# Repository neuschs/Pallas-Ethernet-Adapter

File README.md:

# Pallas-Ethernet-Adapter
Open source PCIe ethernet adapter based on LAN7430

More information can be found on my blog: https://sebis-workshop.de/uncategorized/pallas-ethernet-adapter/

# Ordering and production parameters
So far I've just ordered the PCBAs and waiting to test my prototypes.
In the folder jlcpcb are the files from this KiCAD plugin located:
https://github.com/Bouni/kicad-jlcpcb-tools

Including position correction for some parts so the pick'n'place file is correct (please check before usage).

# Credits
Thanks to the KiCAD PCIe template project:
https://github.com/lucanastasio/PCIexpress-KiCad

# License
All datasheets are just for documentational pruposes here. All credits go to the companys which distributed them initially.

The Logo - the Pallas Cat - may not be redistributed, made public elsewhere or modified and is property of the author. 

This describes Open Hardware and is licensed under the CERN OHL v.1.2.
You may redistribute and modify this under the terms of the CERN OHL v.1.2. (http://ohwr.org/cernohl). This is distributed WITHOUT ANY EXPRESS OR IMPLIED WARRANTY, INCLUDING OF MERCHANTABILITY, SATISFACTORY QUALITY AND FITNESS FOR A PARTICULAR PURPOSE. Please see the CERN OHL v.1.2 for applicable conditions.

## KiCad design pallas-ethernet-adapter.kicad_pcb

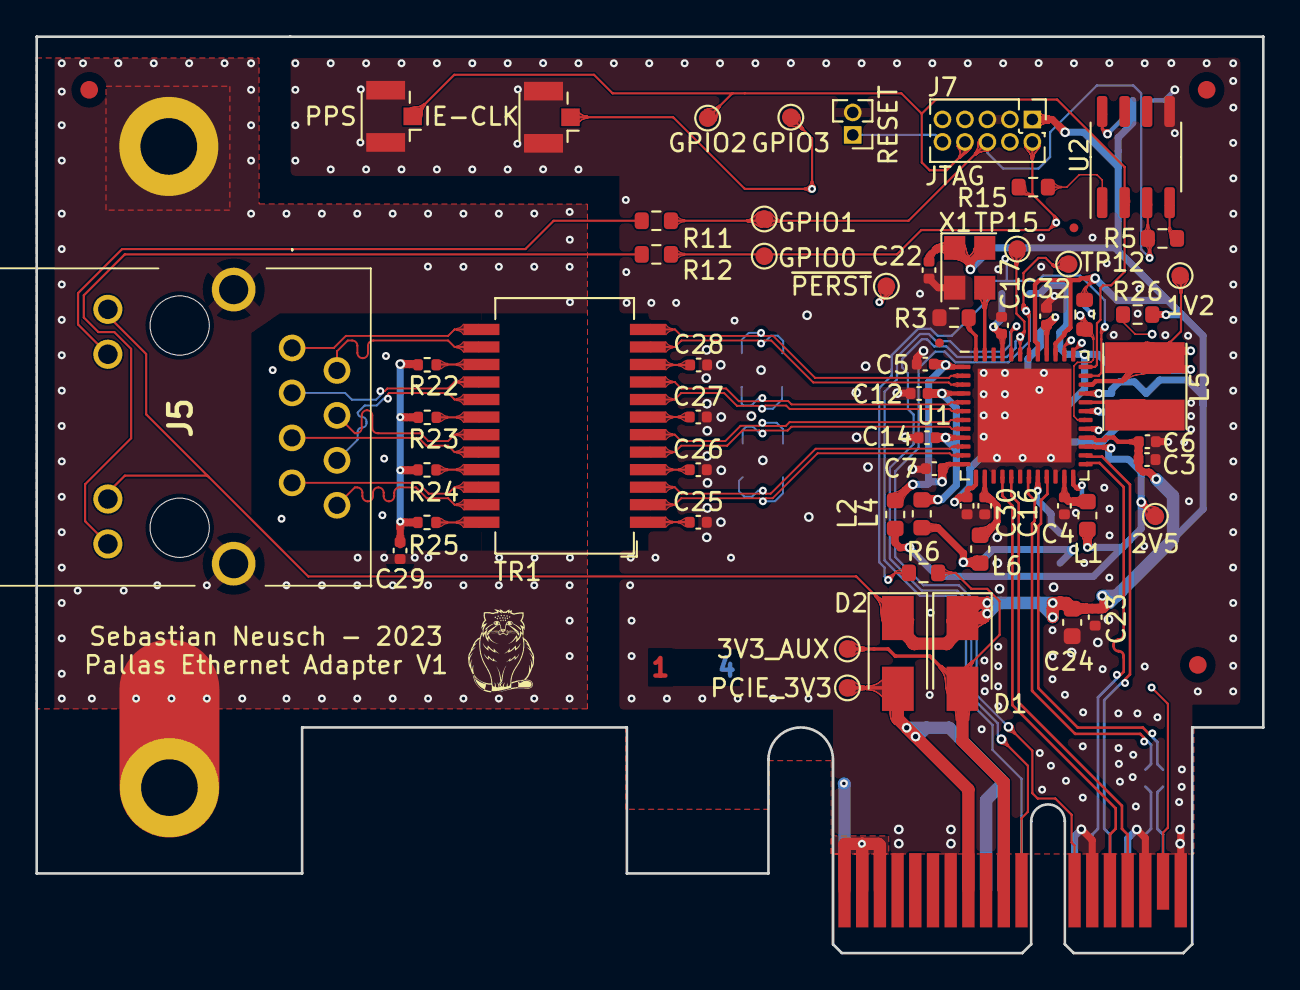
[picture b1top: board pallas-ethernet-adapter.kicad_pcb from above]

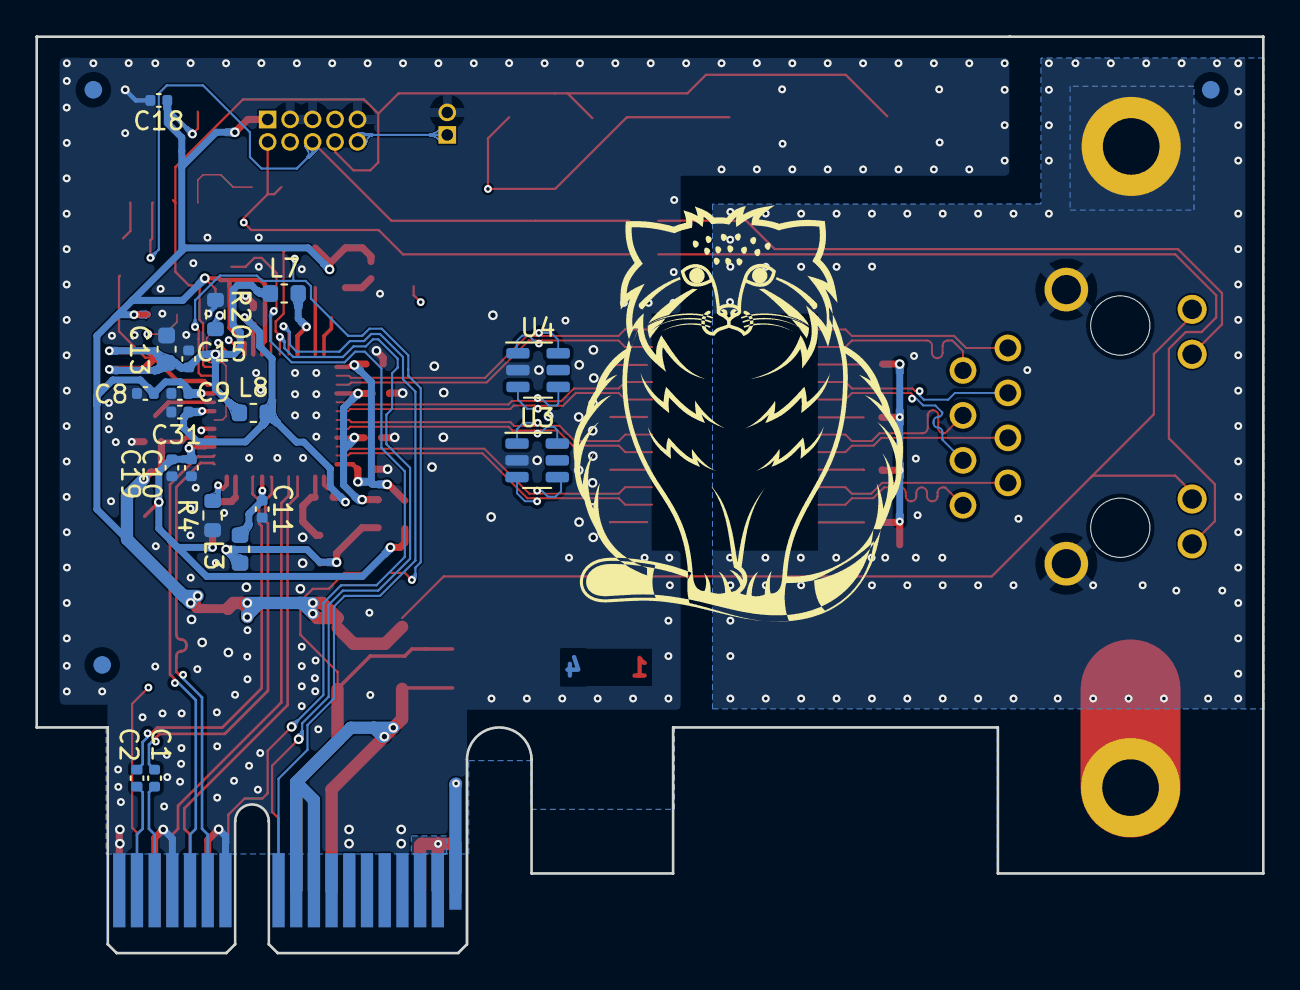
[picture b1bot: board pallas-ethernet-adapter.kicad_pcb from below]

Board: 4 copper layers, 69.3 x 51.8 mm, 88 parts (21 on the bottom side), 66 nets.

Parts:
C1, C2: 100n; C_0402_1005Metric
C3, C8: 4.7uF; C_0402_1005Metric
C4, C5, C6, C7, C9, C11, C12, C14, C15, C16, C17, C18, C19, C22, C23, C25, C26, C27, C28, C29, C30, C31, C32: 100nF; C_0402_1005Metric
C10: 1uF; C_0402_1005Metric
C13, C24: 10uF; C_0603_1608Metric
D1, D2: SS14; D_SMA
FID1, FID2, FID3, FID4, FID5, FID6: Fiducial; Fiducial_1mm_Mask2mm
FID7, FID8: Fiducial; Fiducial_0.5mm_Mask1mm
H1, H2: PCIE_Bracket_Hole; MountingHole_3.2mm_M3_DIN965_Pad
J1: PCIexpress_bracket; PCIexpress_bracket_low
J2: PCIexpress_x1
J3: PPS; U.FL_Hirose_U.FL-R-SMT-1_Vertical
J4: IE-CLK; U.FL_Hirose_U.FL-R-SMT-1_Vertical
J5: RJ45_LED_Shielded; SS74800038F
J6: RESET; PinHeader_1x02_P1.27mm_Vertical
J7: JTAG; PinHeader_2x05_P1.27mm_Vertical
L1, L2, L3, L4, L6, L7, L8: 220R; L_0603_1608Metric
L5: 3.3uH; L_CY43-3.3UH
R3: 6.04k; R_0603_1608Metric
R4: 200; R_0603_1608Metric
R5: 1k; R_0603_1608Metric
R6, R11, R12: 330; R_0603_1608Metric
R15, R19, R20: 0; R_0603_1608Metric
R22, R23, R24, R25: 75; R_0402_1005Metric
R26: 10k; R_0603_1608Metric
TP1: 2V5; TestPoint_Pad_D1.0mm
TP2: 1V2; TestPoint_Pad_D1.0mm
TP3: GPIO3; TestPoint_Pad_D1.0mm
TP4: GPIO2; TestPoint_Pad_D1.0mm
TP5: GPIO1; TestPoint_Pad_D1.0mm
TP6: GPIO0; TestPoint_Pad_D1.0mm
TP10: PCIE_3V3; TestPoint_Pad_D1.0mm
TP12: ~{CLKREQ}; TestPoint_Pad_D1.0mm
TP13: ~{PERST}; TestPoint_Pad_D1.0mm
TP14: 3V3_AUX; TestPoint_Pad_D1.0mm
TP15: ~{WAKE}; TestPoint_Pad_D1.0mm
TR1: MT24-S1T1; Transformer_Ethernet_HALO_TG111-MSC13
U1: LAN7430; QFN-48-1EP_7x7mm_P0.5mm_EP5.3x5.3mm
U2: 93AAxxA; SO-8_3.9x4.9mm_P1.27mm
U3, U4: SRV05-4; SOT-23-6
X1: 25 MHz; OXETGLJANF-25MHZ_FPN

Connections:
+3V3: C3.1, C6.1, C8.1, C9.1, C18.1, C22.1, C23.1, C24.1, D1.1 (K), D2.1 (K), J5.10, J5.12, J7.1 (VTref), R19.2, R26.1, U1.28 (VDD_REG_IN), U1.33 (VDD_SW_IN), U1.39 (VDDVARIO), U1.41 (VDD_OTP), U2.8 (VCC), X1.1 (EN), X1.4 (Vdd)
/CASE: C29.2, H1.1, H2.1, J5.SH
/Ethernet/BOB_SMITH: C29.1, R22.2, R23.2, R24.2, R25.2
/Ethernet/MDI_A_CT: R22.1, TR1.15 (MCT4)
/Ethernet/MDI_A_N: J5.2, TR1.14 (MX4+)
/Ethernet/MDI_A_P: J5.1, TR1.13 (MX4-)
/Ethernet/MDI_B_CT: R23.1, TR1.18 (MCT3)
/Ethernet/MDI_B_N: J5.6, TR1.17 (MTX3+)
/Ethernet/MDI_B_P: J5.3, TR1.16 (MTX3-)
/Ethernet/MDI_C_CT: R24.1, TR1.21 (MCT2)
/Ethernet/MDI_C_N: J5.5, TR1.20 (MTX2+)
/Ethernet/MDI_C_P: J5.4, TR1.19 (MTX2-)
/Ethernet/MDI_D_CT: R25.1, TR1.24 (MTC1)
/Ethernet/MDI_D_N: J5.8, TR1.23 (MTX1+)
/Ethernet/MDI_D_P: J5.7, TR1.22 (MTX1-)
/Ethernet/TXRX_A_CT: C28.1, TR1.10 (TCT4)
/Ethernet/TXRX_A_N: TR1.11 (TD4+), U1.3 (TXRXM_A), U4.1 (I/O1)
/Ethernet/TXRX_A_P: TR1.12 (TD4-), U1.2 (TXRXP_A), U4.6 (I/O4)
/Ethernet/TXRX_B_CT: C27.1, TR1.7 (TCT3)
/Ethernet/TXRX_B_N: TR1.8 (TD3+), U1.6 (TXRXM_B), U4.3 (I/O2)
/Ethernet/TXRX_B_P: TR1.9 (TD3-), U1.5 (TXRXP_B), U4.4 (I/O3)
/Ethernet/TXRX_C_CT: C26.1, TR1.4 (TCT2)
/Ethernet/TXRX_C_N: TR1.5 (TD2+), U1.8 (TXRXM_C), U3.6 (I/O4)
/Ethernet/TXRX_C_P: TR1.6 (TD2-), U1.7 (TXRXP_C), U3.1 (I/O1)
/Ethernet/TXRX_D_CT: C25.1, TR1.1 (TCT1)
/Ethernet/TXRX_D_N: TR1.2 (TD1+), U1.11 (TXRXM_D), U3.3 (I/O2)
/Ethernet/TXRX_D_P: TR1.3 (TD1-), U1.10 (TXRXP_D), U3.4 (I/O3)
/LAN7430/AVDD12: C17.1, L7.2, U1.45 (AVDD12)
/LAN7430/AVDDH: C5.1, C7.1, L2.2, U1.1 (AVDDH_1), U1.12 (AVDDH_2)
/LAN7430/AVDDL: C12.1, C14.1, L4.2, U1.4 (AVDDL_1), U1.9 (AVDDL_2)
/LAN7430/CS: R15.2, U2.1 (CS)
/LAN7430/ISET: R3.2, U1.48 (ISET)
/LAN7430/OSC_OUT: U1.47 (XI), X1.3 (OUT)
/LAN7430/PCIE_CLK_N: J2.A14 (REFCLK-), U1.26 (PCIE_CLK_M)
/LAN7430/PCIE_CLK_P: J2.A13 (REFCLK+), U1.25 (PCIE_CLK_P)
/LAN7430/PCIE_RX_N: J2.B15 (PET0-), U1.17 (PCIE_RX_M)
/LAN7430/PCIE_RX_P: J2.B14 (PET0+), U1.16 (PCIE_RX_P)
/LAN7430/PCIE_TX_N: C2.2, U1.21 (PCIE_TX_M)
/LAN7430/PCIE_TX_P: C1.1, U1.19 (PCIE_TX_P)
/LAN7430/PCIE_VAUX_DET: D1.2 (A), J2.B10 (+3.3V_aux), R6.2, TP14.1
/LAN7430/RESREF: R4.2, U1.24 (RESREF)
/LAN7430/SDO: R5.1, U2.4 (DO)
/LAN7430/TEST: R19.1, R20.2, U1.30 (TEST)
/LAN7430/VDD12CORE: C30.1, C31.1, C32.1, L8.2, U1.13 (VDD12CORE), U1.31 (VDD12CORE), U1.40 (VDD12CORE)
/LAN7430/VDD12_SW_FB: C13.1, C15.1, L3.1, L4.1, L5.2, L6.1, L7.1, L8.1, TP2.1, U1.34 (VDD12_SW_FB)
/LAN7430/VDD12_SW_OUT: L5.1, U1.32 (VDD12_SW_OUT)
/LAN7430/VDD_2V5: C10.1, C19.1, L1.1, L2.1, TP1.1, U1.27 (VDD25_REG_OUT)
/LAN7430/VP: C16.1, L6.2, U1.14 (VP)
/LAN7430/VPH: C4.1, L1.2, U1.23 (VPH)
/LAN7430/VPTX: C11.1, L3.2, U1.20 (VPTX)
/LAN7430/~PCIE_CLKREQ: J2.B12 (nCLKREQ), TP12.1, U1.42 (CLKREQ#)
/LAN7430/~PCIE_PERST: J2.A11 (~PERST), TP13.1, U1.44 (PERST#)
/LAN7430/~PCIE_WAKE: J2.B11 (~WAKE), TP15.1, U1.43 (WAKE#)
/LAN_JTAG_TCK: J4.1 (In), J7.4 (TCK), R6.1, TP3.1, U1.35 (VAUX_DET/GPIO3/LED3/TCK)
/LAN_JTAG_TDI: J7.2 (TMS), R12.1, R15.1, TP6.1, U1.38 (EECS/GPIO0/LED0/TDI)
/LAN_JTAG_TDO: J7.6 (TDO), R5.2, R11.1, TP5.1, U1.37 (EEDIO/GPIO1/LED1/TDO), U2.3 (DI)
/LAN_JTAG_TMS: J3.1 (In), J7.8 (TDI), TP4.1, U1.36 (EECLK/GPIO2/LED2/TMS/ADV_PM_DISABLE), U2.2 (SCLK)
/PCIexpress_connector/3V3: D2.2 (A), J2.A9 (+3.3V), J2.A10 (+3.3V), J2.B8 (+3.3V), TP10.1
/PCIexpress_connector/12V: J2.A2 (+12V), J2.A3 (+12V), J2.B1 (+12V), J2.B2 (+12V), J2.B3 (+12V)
/PCIexpress_connector/_PER0_N: C2.1, J2.A17 (PERn0)
/PCIexpress_connector/_PER0_P: C1.2, J2.A16 (PERp0)
/PCIexpress_connector/~PRSNT1: J2.A1 (~PRSNT1), J2.B17 (~PRSNT2)
/RESET: J6.1, J7.10 (~RESET), R26.2, U1.29 (RESET_N)
/~LED0: J5.11, R12.2
/~LED1: J5.9, R11.2
GND: C3.2, C4.2, C5.2, C6.2, C7.2, C8.2, C9.2, C10.2, C11.2, C12.2, C13.2, C14.2, C15.2, C16.2, C17.2, C18.2, C19.2, C22.2, C23.2, C24.2, C25.2, C26.2, C27.2, C28.2, C30.2, C31.2, C32.2, J2.A4 (GND), J2.A12 (GND), J2.A15 (GND), J2.A18 (GND), J2.B4 (GND), J2.B7 (GND), J2.B13 (GND), J2.B16 (GND), J2.B18 (GND), J3.2 (Ext), J4.2 (Ext), J6.2, J7.3 (GND), J7.5 (GND), J7.9 (GNDDet), R3.1, R4.1, R20.1, U1.15 (GD_1), U1.18 (GD_2), U1.22 (GD_3), U1.49 (EPAD), U2.5 (GND), U3.2 (GND), U4.2 (GND), X1.2 (GND)

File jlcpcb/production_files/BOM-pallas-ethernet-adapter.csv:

Comment,Designator,Footprint,LCSC
93AAxxA,U2,SO-8_3.9x4.9mm_P1.27mm,C153277
0,"R15,R20",R_0603_1608Metric,C21189
1k,R5,R_0603_1608Metric,C21190
330,"R11,R12,R6",R_0603_1608Metric,C23138
4.7uF,"C3,C8",C_0402_1005Metric,C23733
SS14,"D1,D2",D_SMA,C2480
75,"R22,R23,R24,R25",R_0402_1005Metric,C25133
10k,R26,R_0603_1608Metric,C25804
3.3uH,L5,L_CY43-3.3UH,C2929417
25 MHz ,X1,OXETGLJANF-25MHZ_FPN,C295525
100n,"C1,C11,C12,C14,C15,C16,C17,C18,C19,C2,C22,C23,C25,C26,C27,C28,C29,C30,C31,C32,C4,C5,C6,C7,C9",C_0402_1005Metric,C307331
6.04k,R3,R_0603_1608Metric,C325745
SRV05-4,"U3,U4",SOT-23-6,C397788
MT24-S1T1,TR1,Transformer_Ethernet_HALO_TG111-MSC13,C501477
1uF,C10,C_0402_1005Metric,C52923
LAN7430,U1,QFN-48-1EP_7x7mm_P0.5mm_EP5.3x5.3mm,C633486
200,R4,R_0603_1608Metric,C8218
PPS,"J3,J4",U.FL_Hirose_U.FL-R-SMT-1_Vertical,C88373
220R,"L1,L2,L3,L4,L6,L7,L8",L_0603_1608Metric,C88971
10uF,"C13,C24",C_0603_1608Metric,C96446
PCIexpress_bracket,J1,PCIexpress_bracket_low,
RESET,J6,PinHeader_1x02_P1.27mm_Vertical,
JTAG,J7,PinHeader_2x05_P1.27mm_Vertical,
RJ45_LED_Shielded,J5,SS74800038F,

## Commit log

2023-01-17 initial commit 98%
2023-01-17 really added all the files not like last time
2023-01-19 * ground plane change to keep out beneath the magnetic module * changed RJ45 modular jack from tab up to tab down to improve the routing * added an 3d modell in the library folder for the rj45 connec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
2023-01-20 * modified .gitignore to exclude backup zip files * removed existing backup files
2023-01-20 * moved magnetics to RJ45 connector for better EMI performance (still not enough though) * changed keepout layer beneath magnetics * moved meanders from magnetic side to connector side (from matched 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
2023-01-20 * corrected some drc errors like hole clearance, unconnected tracks etc.. * added screenshots of the impedance calculation in regards of the JLCPCB 3313 stackup * added picture of rendered 3d perspec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
2023-01-20 * changed license to exclude the pallas cat logo * added the logo to the pcb as front and back silkscreen
2023-01-20 * corrected angle data in the jlcpcb plugin data * generated near final gerber files - waiting for release by a peer partner
2023-01-29 * generated production files new * added bom and cpl pick and place file (previous not included)
2023-02-16 * removed R19 from jlcpcb CPL (PNP File) and from BOM fix: #2 * widened the holes for the RH45 connector by 0.1mm fix: #5 * added datasheets to documentation directory as well as a dummy graphic for 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
2023-02-16 * repoured all copper zones and reexported production files to accomodate last changes
2023-02-16 * updated readme
2023-02-16 * created initial configuration file with the two LEDs * LED0 & LED1 activated as Link/Activity and Link1000/Activity * deactivated EnergySave Power Mode * ATTENTION the eeprom-dump.bin file contains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
2023-02-18 * added bracket in stl and step format fix: #4 * fixed hole size of rj45 finally fix: #5
2023-02-18 * created manufacuring files for past changes
